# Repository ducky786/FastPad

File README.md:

# FASTPAD

My project is a simple macropad that consists of 5 buttons, a rotary incoder a slider and a .95" oled display all powerd by a xiao 2040!. 
I made this project beucase I found myself constantly struggling with navigating around in my divice. I wouold be slow in changing tabs, closing tabs ext. So, I wanted
to make this so I can navigate faster and more efficently. I also plan on using this micropad as a small controle board for future projects. It has sufficent 
number of buttons and incoders to create a diverse range of actions paired with an oled screen for veiwing information. In short I hope to use this macropad for a variety 
diffrent things that can help me on productivity and combine with future projects to take them to a next level!!!

# PCB:
This was my first time building a PCB so the connections look very messy!

# Frameware
* Slider controles volume
* rotary encoder toggles through diffrent tabs
* 5 buttons, so far only decided on 3 buttons: copy, past, open vscode
* Not sure what to use the Oled screen to display.
I will deffenetly be changing the button macros depending on what I do later on.

# CAD
I Made half of the case in onshape but after facing trouble with the software I moved my progress to Fusion360! The case is made up of 2 3D printed parts the top and the bottom. They are both held together with M3x16mm screws M3x5mx4mm heatset inserts! 
I really loved how this turned out beucase it was my first time cadding and this took the most time in the whole project! very happy with the results!!! 
I didnt exactly know what to name it so I named it fast pad beucase I made it to help me be faster in productivity with shortcuts! :)

# BOM
* 1x xiao 2040
* 5x mx switches: [MX Switches](https://mechanicalkeyboards.com/products/cherry-mx-brown-hyperglide-45g-tactile?_pos=6&_sid=95f310540&_ss=r)
* 5x Blank DSA keycaps (White)
* 1x .96" oled screen: [oled screen](https://www.aliexpress.us/item/3256805954920554.html?spm=a2g0o.productlist.main.4.404f2441YCMLtk&aem_p4p_detail=202506111438272540227140291600001683197&algo_pvid=e33161a7-fe95-4cb0-9fe0-f14535a81582&algo_exp_id=e33161a7-fe95-4cb0-9fe0-f14535a81582-3&pdp_ext_f=%7B"order"%3A"3155"%2C"eval"%3A"1"%7D&pdp_npi=4%40dis%21USD%212.22%212.02%21%21%2115.90%2114.47%21%402103146f17496779077843997efe5d%2112000035944225408%21sea%21US%210%21ABX&curPageLogUid=VVvtdeTjFJQ1&utparam-url=scene%3Asearch%7Cquery_from%3A&search_p4p_id=202506111438272540227140291600001683197_2&_gl=1*1rxylgr*_gcl_au*NjYxNDYwOTA4LjE3NDk2NzUxOTQ.*_ga*MjcwMjExMTkzLjE3NDk2NzUxOTQ.*_ga_VED1YSGNC7*czE3NDk2Nzc4ODgkbzIkZzEkdDE3NDk2Nzc5MDgkajQwJGwwJGgw)
* 1x slide Potentiomiter: [slider](https://www.mouser.com/ProductDetail/Bourns/PTL30-15R1-104B2?qs=b8viKDOLiXZRUw8o0OtIKw%3D%3D&srsltid=AfmBOopoE0hObKvTDaviANXkcjZPlvkvTbKF7ejl5Zsrhthjv9kuD8vu)
* 1x slider keycap: [slider cap](https://www.amazon.com/ezqnirk-10PCS-Mixer-Straight-Potentiometer/dp/B0CLD3T5TN/ref=sr_1_16?crid=3PFH9VSNJOVLJ&dib=eyJ2IjoiMSJ9.vFCWhD2FO888_roA338KFnGPGHrYowEs66kdVQP-jPqUbMepofR9MplnJZ-yfvW_2c0ITgr9VxyoRx1DGslyXfsUo8KQp1sndo_gjvT_vujOzdakJncuEJmu2JM8YLBNUh9mKVzZufOnXLxUUV4gT6IzQ-jEWR-VeebbS6LYet2U0NKvVNncd46uym8sSym1DrRmaOhYy5PlburNjWUTP8m2bHBHbPPgDPUCS8pyJwo.k1ZLgtzwTcqIg9JDznZ09IcSoM5O9TkMRmkt9C1dFn4&dib_tag=se&keywords=slider+keycap&qid=1749678257&sprefix=slider+keycap%2Caps%2C106&sr=8-16)
* 1x Push button rotary encoder: [Encoder](https://www.amazon.com/Adafruit-Accessories-Rotary-Encoder-piece/dp/B00SK8KK5Y)
* 4x M3x16mm screws
* 8x M3x5mx4mm heatset inserts
* 1x Case (2 3D printed parts, TOP and BOTTOM)

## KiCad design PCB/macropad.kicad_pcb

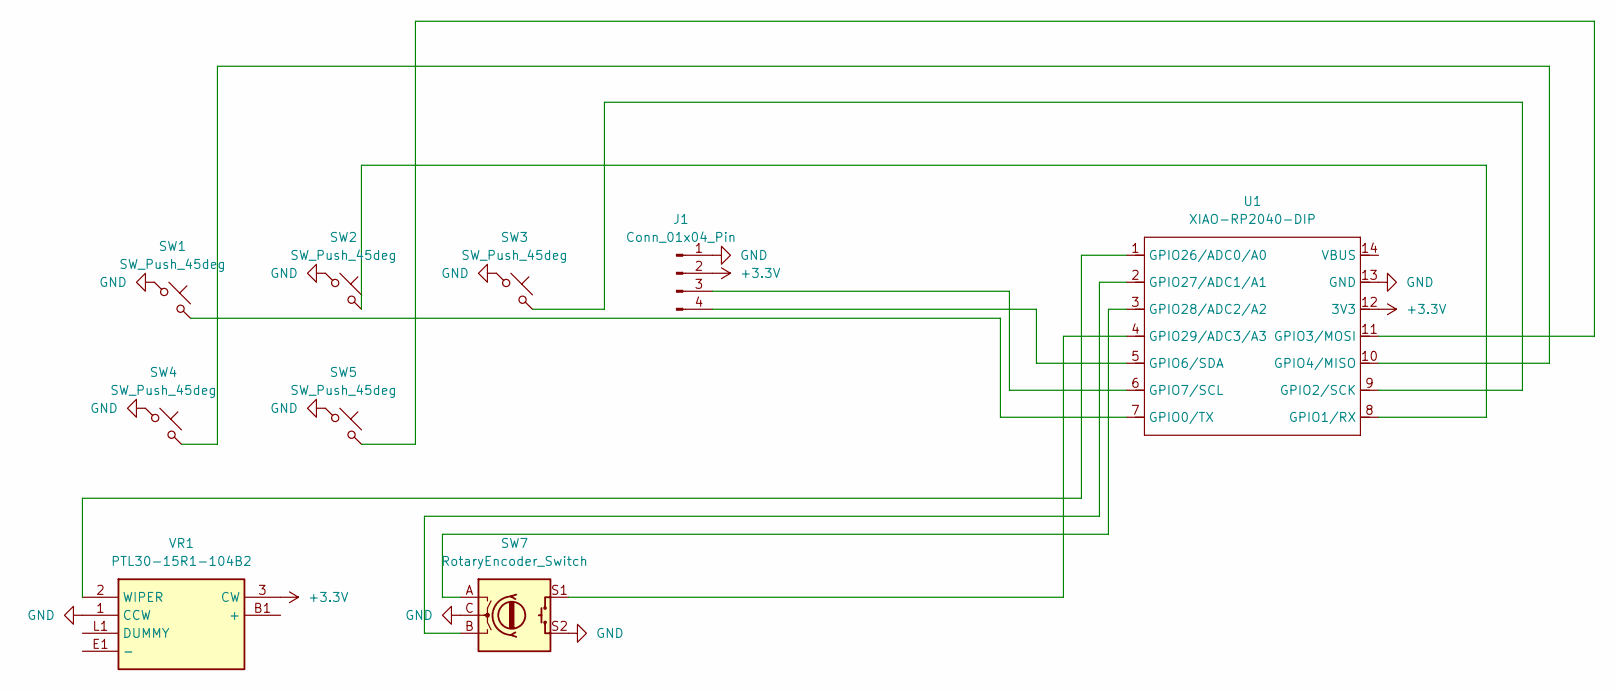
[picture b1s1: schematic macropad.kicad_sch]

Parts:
J1: Conn_01x04_Pin; 128x64OLED
SW1, SW2, SW3, SW4, SW5: SW_Push_45deg; SW_Cherry_MX_1.00u_PCB_SWITCHON
SW7: RotaryEncoder_Switch; RotaryEncoder_Alps_EC11E-Switch_Vertical_H20mm_CircularMoun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
U1: XIAO-RP2040-DIP
VR1: PTL30-15R1-104B2; PTL3015R1104B2; Mouser Part Number 652-PTL30-15R1-104B2

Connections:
+3.3V: J1.2, U1.12 (3V3), VR1.3 (CW)
GND: J1.1, SW1.1, SW2.1, SW3.1, SW4.1, SW5.1, SW7.C, SW7.S2, U1.13 (GND), VR1.1 (CCW)
unnamed: J1.3, U1.6 (GPIO7/SCL)
unnamed: J1.4, U1.5 (GPIO6/SDA)
unnamed: SW1.2, U1.7 (GPIO0/TX)
unnamed: SW2.2, U1.8 (GPIO1/RX)
unnamed: SW3.2, U1.9 (GPIO2/SCK)
unnamed: SW5.2, U1.11 (GPIO3/MOSI)
unnamed: SW4.2, U1.10 (GPIO4/MISO)
unnamed: U1.1 (GPIO26/ADC0/A0), VR1.2 (WIPER)
unnamed: SW7.B, U1.2 (GPIO27/ADC1/A1)
unnamed: SW7.A, U1.3 (GPIO28/ADC2/A2)
unnamed: SW7.S1, U1.4 (GPIO29/ADC3/A3)

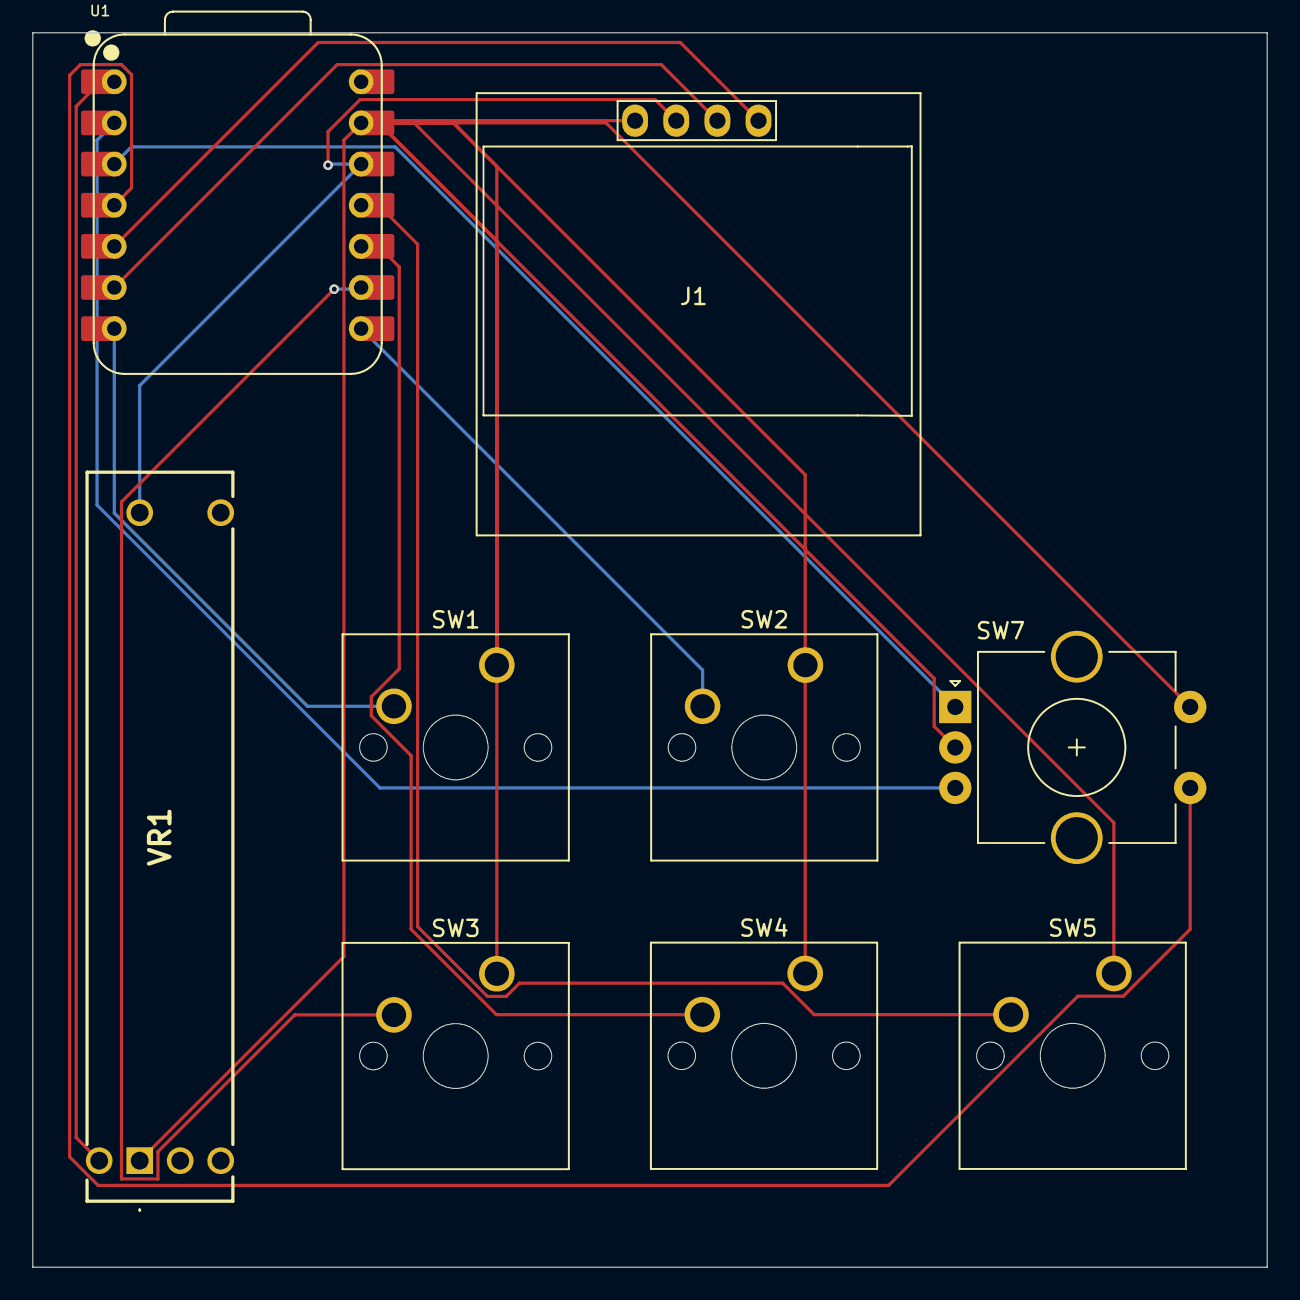
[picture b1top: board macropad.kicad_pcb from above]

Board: 2 copper layers, 76.2 x 76.2 mm, 9 parts (0 on the bottom side), 13 nets.

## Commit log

2025-06-12 Create Macropad_Top
2025-06-12 Create zip
2025-06-12 Create w
